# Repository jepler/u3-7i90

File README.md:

# u3-7i90

This repository will hold the design files for the level adaptor from ODROID U3 to Mesa 7i90, as well as instructions on building a Linux kernel for the ODROID with the necessary customizations.

# Development status

The author (@jepler) is not actively using or developing this project.
Issues and pull requests are not likely to be acted on.
I would be interested in passing this project to a new maintainer.

# The board

<a href="https://oshpark.com/shared_projects/QzWVEFEG"></img></a>
(I do not receive any compensation from oshpark when you order my design)

## Theory

The TXB0104 level translator is used for voltage conversion between the ODROID (1.8v I/O standard) and 7i90 (3.3v I/O standard).  I had success running at up to 40MHz, but by the TXB datasheet a safe rate is more like 30MHz.  (in any case, even at 30MHz, setup / cleanup time dominates SPI transaction time so choose a reliable rate rather than a fast one)

## Design Files

The board was designed in Eagle 6.6.  The board files may not be readable in earlier versions.

## Assembling and installing the board

Most of the assembly should be straightforward.  Two things to note:

 * You MUST use appropriate spacers between the two boards to keep the connectors well-aligned.  The 2mm connectors are fragile; I ruined them and had to rework the board, which was not a lot of fun.
 * The connectors go on the top (owl) side, the surface-mount parts go on the bottom (blank) side.
 * I recommend that you work in this order:
  * Solder all items but the connectors
  * Insert the 2mm male headers into the odroid's female headers
  * put the level adapter board on top with the spacers in between
  * solder the 2mm male headers onto the level adapter board
  * solder the 26-pin header

This assembly method is somewhat forgiving of overlong spacers, as long as some of the solder tail of the male headers still sticks into the board.  You want to avoid using too-short spacers, as this will flex the boards.  In theory the assembly distance should be 6mm.

# The software 
## OS
I use the Ubuntu 14.04 image from hardkernel, but probably a debian userspace would work just as well.

## Kernel

You'll have to build your own kernel; there's no packaged kernel at this time.

Use the kernel source tree at https://github.com/jepler/odroid-linux, branch odroid-3.8.13-rt.  The configuration you want is `arch/arm/configs/odroidu_defconfig`.  I build the kernels on an amd64 debian machine using an arm compiler from gcc-4.7-arm-linux-gnueabihf.

TODO: add links to installation instructions; split cross-scripts out 

cross configuring script:

```
ARCH=arm make ${1-menuconfig}
```

cross building script:

```
#!/bin/bash
set -xe

extraversion=

export ARCH=arm
export DEB_HOST_ARCH=armhf

export CONCURRENCY_LEVEL=`getconf _NPROCESSORS_ONLN`
fakeroot make-kpkg --arch arm --cross-compile arm-linux-gnueabihf- --initrd ${extraversion:+--append-to-version=$extraversion} kernel_image kernel_headers

make ARCH=arm CROSS_COMPILE=arm-linux-gnueabihf- ${extraversion:+EXTRAVERSION=$extraversion} zImage
cp arch/arm/boot/zImage ../zImage
```

### Known problems

The kernel crashes when it receives a byte on the serial terminal.  However,
early boot messages can still be seen via the serial port if necessary, and
of course you can intercept uboot and boot the original kernel if you really
need to interact via the serial console.

## Misc files

`misc-files` contains important files I've customized.

## LinuxCNC

Use LinuxCNC master branch configured for uspace.  Everything should be just
about normal.

Consider booting with isolcpus=3 to improve latency a bit.

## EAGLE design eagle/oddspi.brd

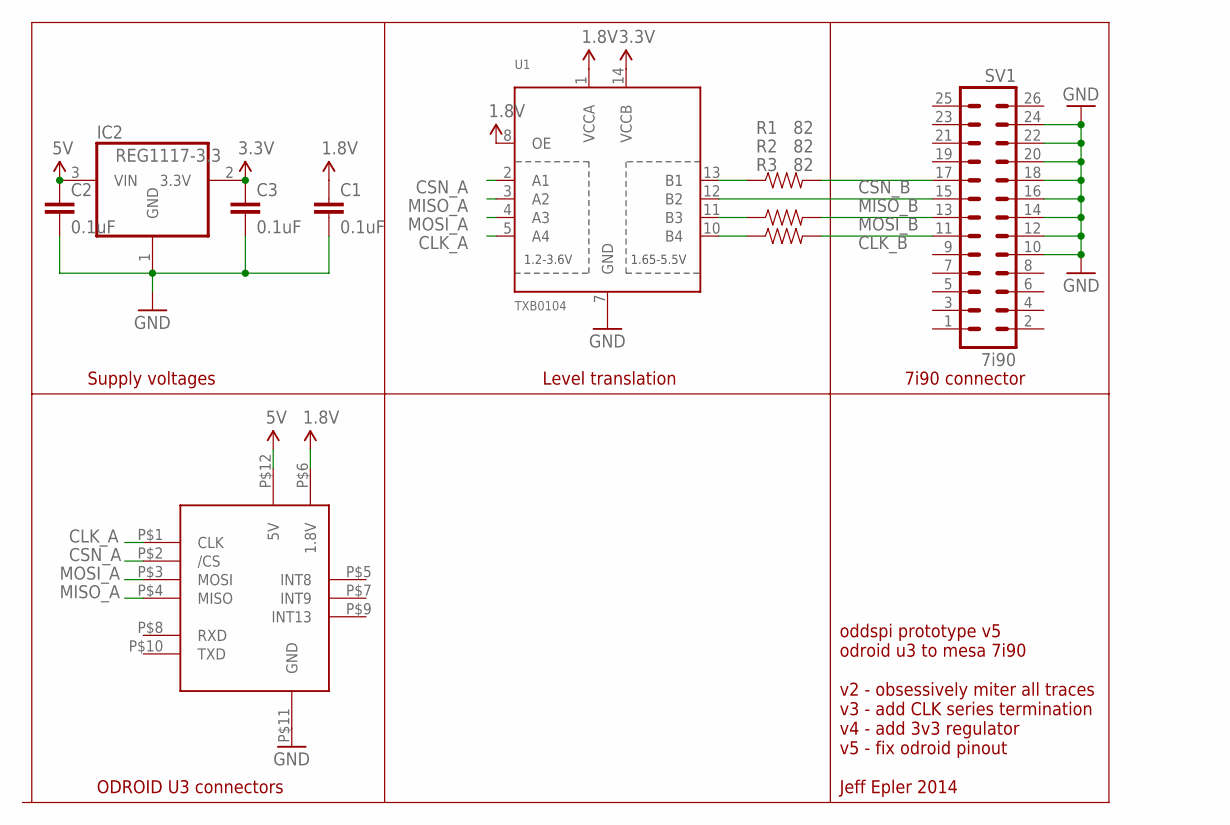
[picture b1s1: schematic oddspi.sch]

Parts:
C1, C2, C3: 0.1uF; 0603-CAP
IC2: REG1117-3.3; SOT223
R1, R2, R3: 82; 0603-RES
SV1: 7i90; ML26
U1: TXB0104; SO14
U$4: ODROID-U3; U3V05

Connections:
1.8V: C1.1, U1.1 (VCCA), U1.8 (OE), U$4.P$6 (1.8V)
3.3V: C3.1, IC2.2 (3.3V), U1.14 (VCCB)
5V: C2.1, IC2.3 (VIN), U$4.P$12 (5V)
CLK_A: U1.5 (A4), U$4.P$1 (CLK)
CLK_B: R1.2, SV1.11
CSN_A: U1.2 (A1), U$4.P$2 (/CS)
CSN_B: R3.2, SV1.17
GND: C1.2, C2.2, C3.2, IC2.1 (GND), SV1.10, SV1.12, SV1.14, SV1.16, SV1.18, SV1.20, SV1.22, SV1.24, U1.7 (GND), U$4.P$11 (GND)
MISO_A: U1.3 (A2), U$4.P$4 (MISO)
MISO_B: SV1.15, U1.12 (B2)
MOSI_A: U1.4 (A3), U$4.P$3 (MOSI)
MOSI_B: R2.2, SV1.13
unnamed: R1.1, U1.10 (B4)
unnamed: R3.1, U1.13 (B1)
unnamed: R2.1, U1.11 (B3)

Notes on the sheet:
ODROID U3 connectors
Supply voltages
Level translation
7i90 connector
oddspi prototype v5 odroid u3 to mesa 7i90 v2 - obsessively miter all traces v3 - add CLK series termination v4 - add 3v3 regulator v5 - fix odroid pinout Jeff Epler 2014

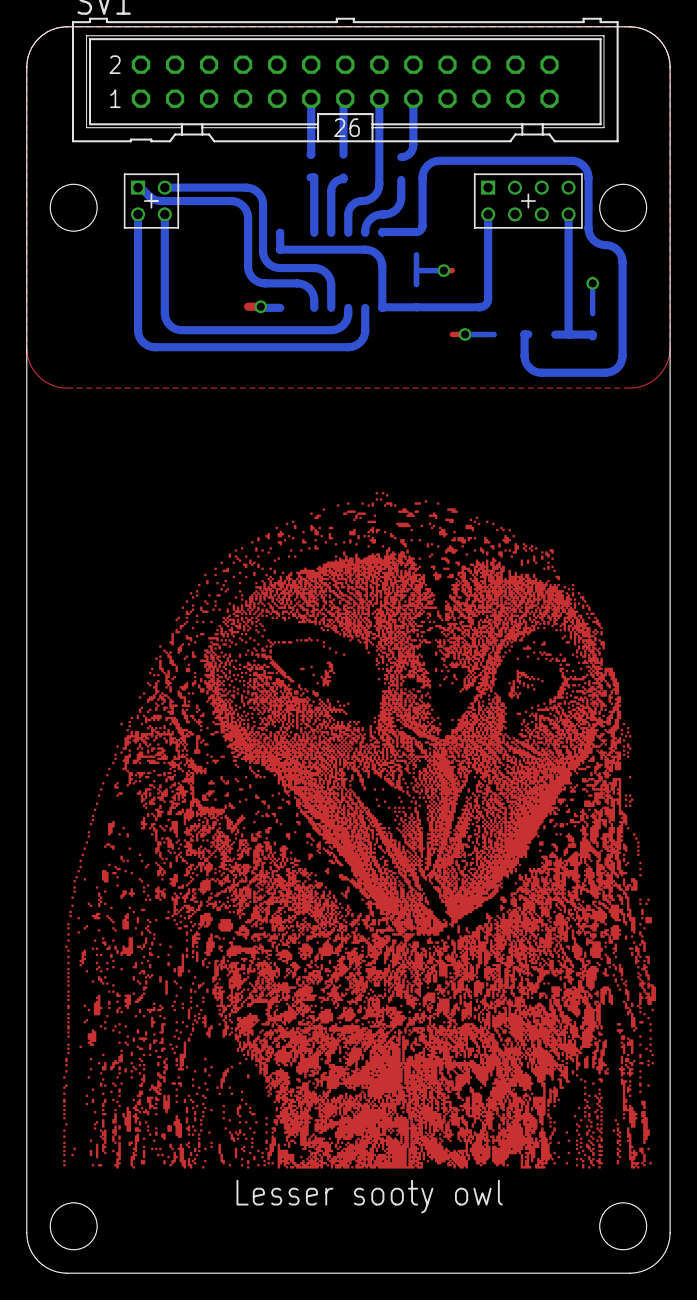
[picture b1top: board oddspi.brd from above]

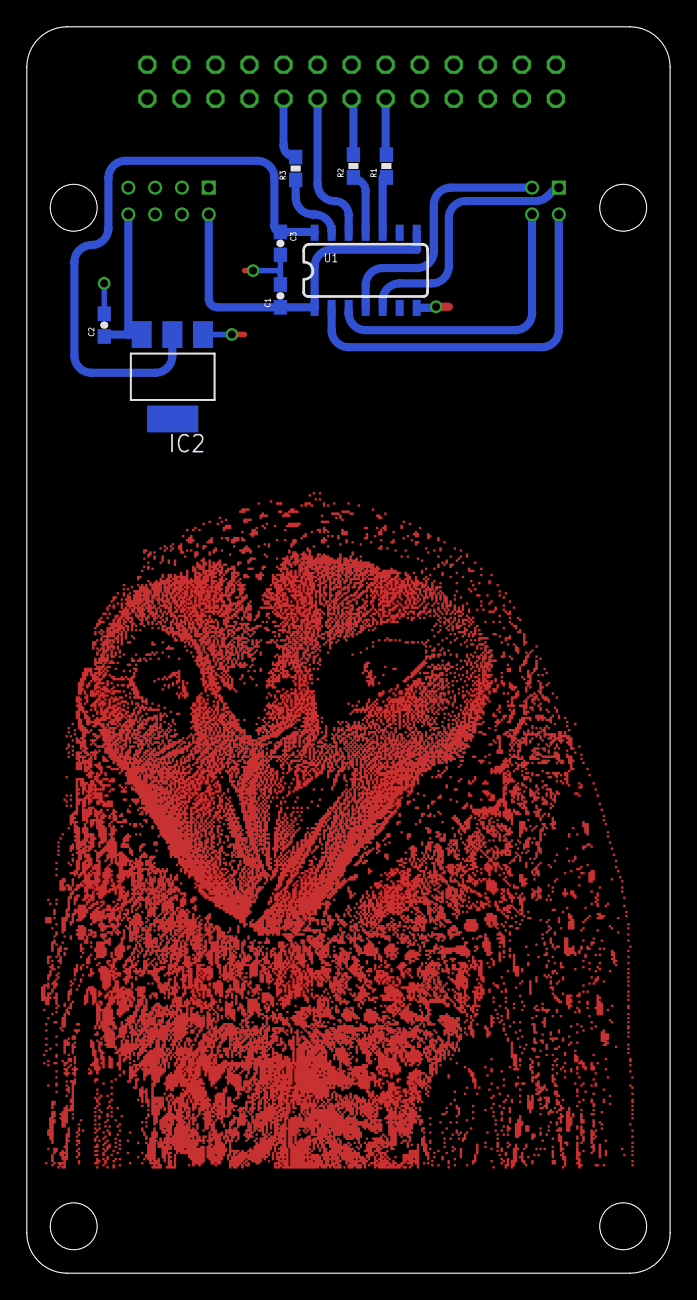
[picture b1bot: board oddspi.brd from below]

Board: 2 copper layers, 48.0 x 93.0 mm, 10 parts (8 on the bottom side), 15 nets.

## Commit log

2014-09-17 files used in eagle to make the board
2014-09-17 result of printing the schematic and board in eagle
2014-09-17 A note about the board assembly
2014-09-17 update notes
2014-10-08 add some important modified files from /etc
2014-10-08 ugh, the serial console's broken
2016-09-12 add order link (oshpark)
2017-05-03 Add a note about development status

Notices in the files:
parts and their libraries:
SparkFun-Capacitors: Licensing: Creative Commons ShareAlike 4.0 International - https://creativecommons.org/licenses/by-sa/4.0
SparkFun: Licensing: CC v3.0 Share-Alike You are welcome to use this library for commercial purposes.
